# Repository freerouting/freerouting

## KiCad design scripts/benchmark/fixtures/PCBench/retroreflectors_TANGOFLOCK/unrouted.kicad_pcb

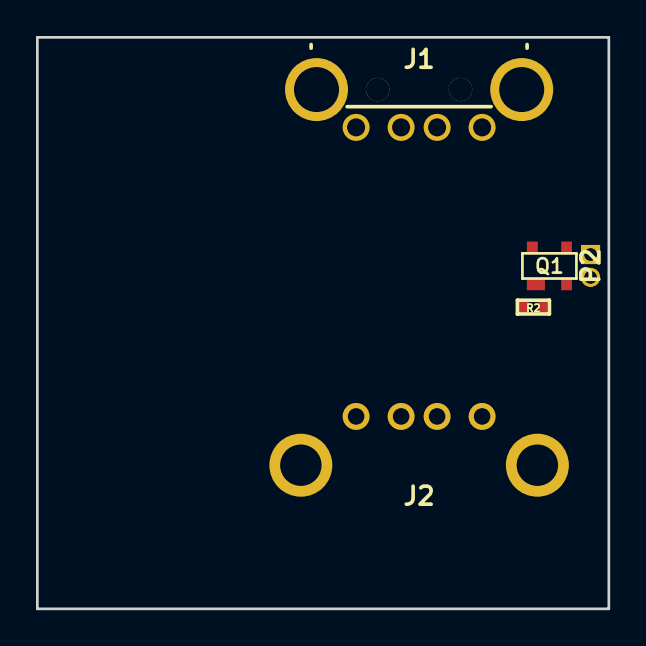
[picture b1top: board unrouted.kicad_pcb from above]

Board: 2 copper layers, 31.8 x 31.8 mm, 5 parts (0 on the bottom side), 6 nets, no tracks yet.

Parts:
J1: USB-DEVICE-SHIELD; GSG-USB-A-1001-010-01001-SHIELD
J2: USB-DEVICE-SHIELD; GSG-USB-A1HSW6
P2: ANTENNA; GSG-50MIL-HEADER-1x2-TH
Q1: MOSFET_N; GSG-SOT143B-GDS
R2: 10k; GSG-0402

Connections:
/DRAIN: P2.1, Q1.D
/GATE: J1.3, J2.3, Q1.G, R2.1
/SHIELD: J1.5, J2.5
GND: J1.4, J2.4, P2.2, Q1.B, Q1.S, R2.2
unnamed: J1.1, J2.1
unnamed: J1.2, J2.2

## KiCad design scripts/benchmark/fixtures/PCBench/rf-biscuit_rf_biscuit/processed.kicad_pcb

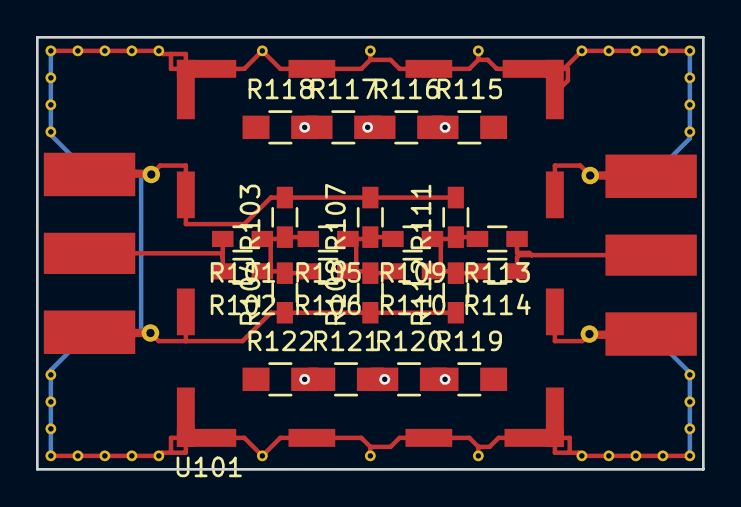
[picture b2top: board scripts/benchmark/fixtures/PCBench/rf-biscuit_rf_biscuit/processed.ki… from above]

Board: 2 copper layers, 37.0 x 24.0 mm, 25 parts (0 on the bottom side), 12 nets.

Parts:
P101, P102: BNC; SMA_EDGE_CONNECTOR
R101, R102, R103, R104, R105, R106, R107, R108, R109, R110, R111, R112, R113, R114: R; R_0603_HandSoldering
R115, R116, R117, R118, R119, R120, R121, R122: R; R_0805_HandSoldering
U101: 36103205_HF_Shield; 36103205-HF_Shield

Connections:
GND: P101.2, P102.2, R103.2, R104.1, R107.2, R108.1, R111.2, R112.1, U101.1
unnamed: P101.1, R101.2, R102.2
unnamed: P102.1, R113.1, R114.1
unnamed: R101.1, R102.1, R103.1, R104.2, R105.2, R106.2
unnamed: R105.1, R106.1, R107.1, R108.2, R109.2, R110.2
unnamed: R109.1, R110.1, R111.1, R112.2, R113.2, R114.2
unnamed: R115.1, R116.2
unnamed: R116.1, R117.2
unnamed: R117.1, R118.2
unnamed: R119.1, R120.2
unnamed: R120.1, R121.2
unnamed: R121.1, R122.2

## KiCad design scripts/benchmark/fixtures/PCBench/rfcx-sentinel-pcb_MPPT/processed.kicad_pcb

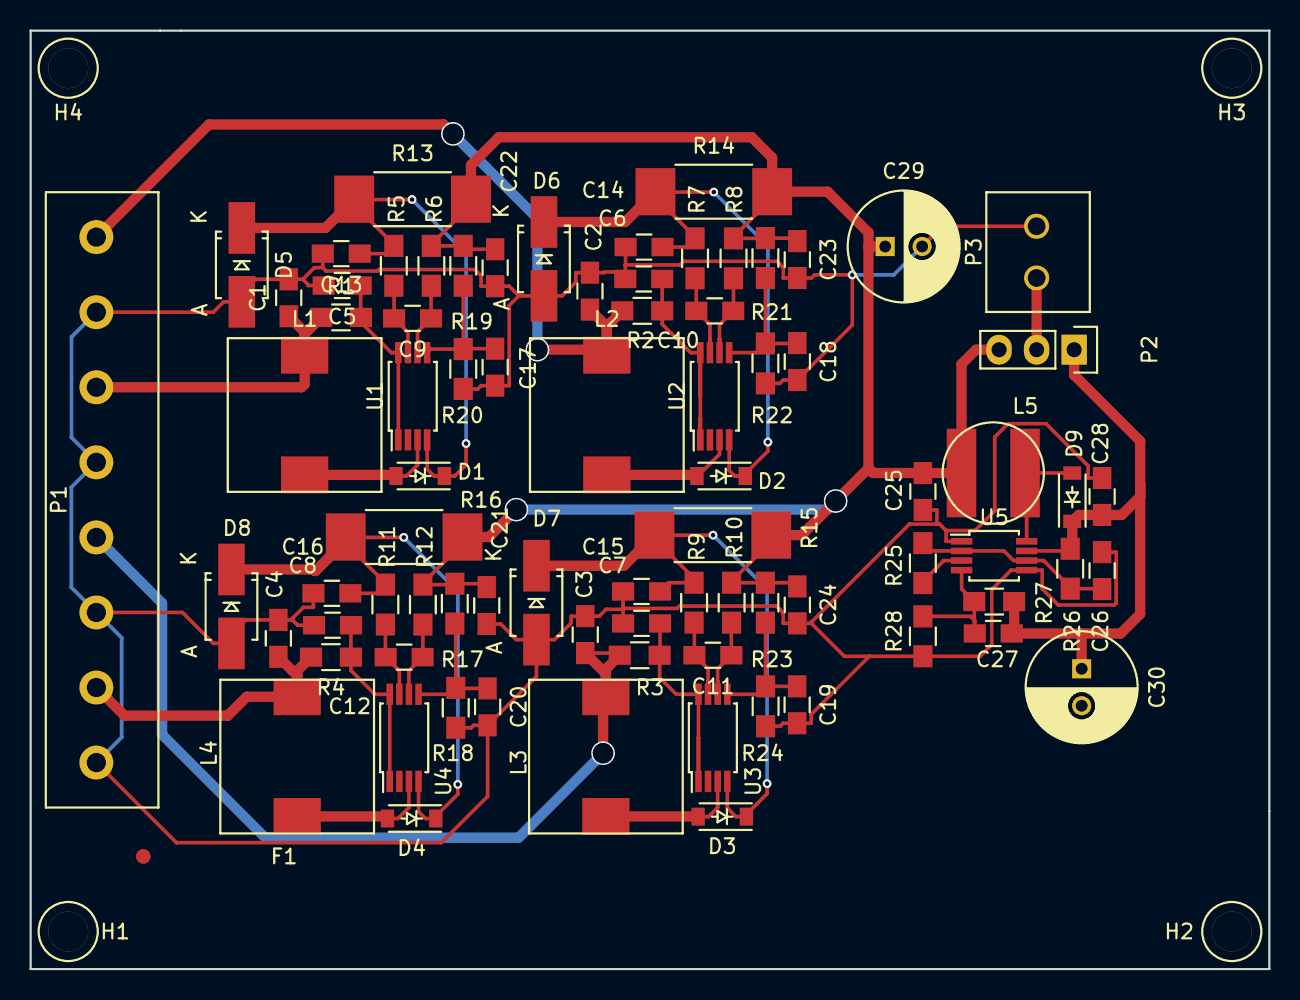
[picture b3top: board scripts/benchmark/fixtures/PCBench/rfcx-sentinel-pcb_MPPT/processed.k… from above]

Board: 2 copper layers, 83.8 x 63.5 mm, 86 parts (1 on the bottom side), 36 nets.

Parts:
C1, C2, C3, C4, C21, C22, C23, C24: 10uF; C_0805_HandSoldering
C5, C6, C7, C8: 100nF; C_0805_HandSoldering
C9, C10, C11, C12, C26: 1uF; C_0805_HandSoldering
C13, C14, C15, C16: 4.7uF; C_0805_HandSoldering
C17, C18, C19, C20: 1nF; C_0805_HandSoldering
C25: 22uF; C_0805_HandSoldering
C27: 39pF; C_0805_HandSoldering
C28: 68uF Tant; C_0805_HandSoldering
C29, C30: DNP; C_Radial_D7.5_L11.2_P2.5
D1, D2, D3, D4: 1n5819; SOD-123
D5, D6, D7, D8: Diode-TVS; Diode-SMA_Handsoldering
D9: 1N5819; SOD-123
F1: Fiducial; Fiducial_1mm_Dia_2.54mm_Outer_CopperTop
H1, H2, H3, H4: Mounting_Hole; Mnt_Hole
L1, L2, L3, L4: 10uH; Ind_10_4x10_4
L5: 6.8uF; Ind_6x6
Noname_1: Symbol_OSHW-Logo_SilkScreen
P1: CONN_01X08; Terminal_Block_8
P2: CONN_01X03; Pin_Header_Straight_1x03
P3: CONN_01X02; TerminalBlock_2
R1, R2, R3, R4, R5, R6, R7, R8, R9, R10, R11, R12: 1k; R_0805_HandSoldering
R13, R14, R15, R16: 0.5, 2W; R_2512_HandSoldering
R17, R19, R21, R23: 330K; R_0805_HandSoldering
R18, R20, R22, R24: 121K; R_0805_HandSoldering
R25: 200K; R_0805_HandSoldering
R26: 49.9; R_0805_HandSoldering
R27: 150K; R_0805_HandSoldering
R28: 49.9K; R_0805_HandSoldering
U1, U2, U3, U4: SPV1040; TSSOP-8_4.4x3mm_Pitch0.65mm
U5: LMR61428; MSOP-8_3x3mm_Pitch0.65mm

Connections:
/LM_FB: C27.1, R27.2, R28.1, U5.4
/MPPT_OUT: C21.1, C22.1, C23.1, C24.1, C25.1, C29.1, L5.1, P2.3, R6.2, R8.2, R10.2, R12.2, R13.2, R14.2, R15.2, R16.2, R17.1, R19.1, R21.1, R23.1
/Panel_Out_V: C27.2, C28.1, C30.1, D9.1, P2.1, R26.1, R27.1, U5.7
GND: C1.2, C2.2, C3.2, C4.2, C5.2, C6.2, C7.2, C8.2, C13.2, C14.2, C15.2, C16.2, C17.2, C18.2, C19.2, C20.2, C21.2, C22.2, C23.2, C24.2, C25.2, C26.2, C28.2, C29.2, D5.2, D6.2, D7.2, D8.2, P1.2, P1.4, P1.6, P1.8, P3.2, R18.2, R20.2, R22.2, R24.2, R28.2, U5.1, U5.5
unnamed: C1.1, L1.1, P1.3, R1.1
unnamed: C2.1, L2.1, P1.1, R2.1
unnamed: C3.1, L3.1, P1.5, R3.1
unnamed: C4.1, L4.1, P1.7, R4.1
unnamed: C5.1, R1.2, U1.1, U1.8
unnamed: C6.1, R2.2, U2.1, U2.8
unnamed: C7.1, R3.2, U3.1, U3.8
unnamed: C8.1, R4.2, U4.1, U4.8
unnamed: C9.1, R6.1, U1.6
unnamed: C9.2, R5.1, U1.7
unnamed: C10.1, R8.1, U2.6
unnamed: C10.2, R7.1, U2.7
unnamed: C11.1, R10.1, U3.6
unnamed: C11.2, R9.1, U3.7
unnamed: C12.1, R12.1, U4.6
unnamed: C12.2, R11.1, U4.7
unnamed: C13.1, D1.1, D5.1, R5.2, R13.1, U1.4
unnamed: C14.1, D2.1, D6.1, R7.2, R14.1, U2.4
unnamed: C15.1, D3.1, D7.1, R9.2, R15.1, U3.4
unnamed: C16.1, D4.1, D8.1, R11.2, R16.1, U4.4
unnamed: C17.1, R19.2, R20.1, U1.5
unnamed: C18.1, R21.2, R22.1, U2.5
unnamed: C19.1, R23.2, R24.1, U3.5
unnamed: C20.1, R17.2, R18.1, U4.5
unnamed: C26.1, R25.1, R26.2, U5.2, U5.6
unnamed: D1.2, L1.2, U1.3
unnamed: D2.2, L2.2, U2.3
unnamed: D3.2, L3.2, U3.3
unnamed: D4.2, L4.2, U4.3
unnamed: D9.2, L5.2, U5.8
unnamed: P2.2, P3.1
unnamed: R25.2, U5.3

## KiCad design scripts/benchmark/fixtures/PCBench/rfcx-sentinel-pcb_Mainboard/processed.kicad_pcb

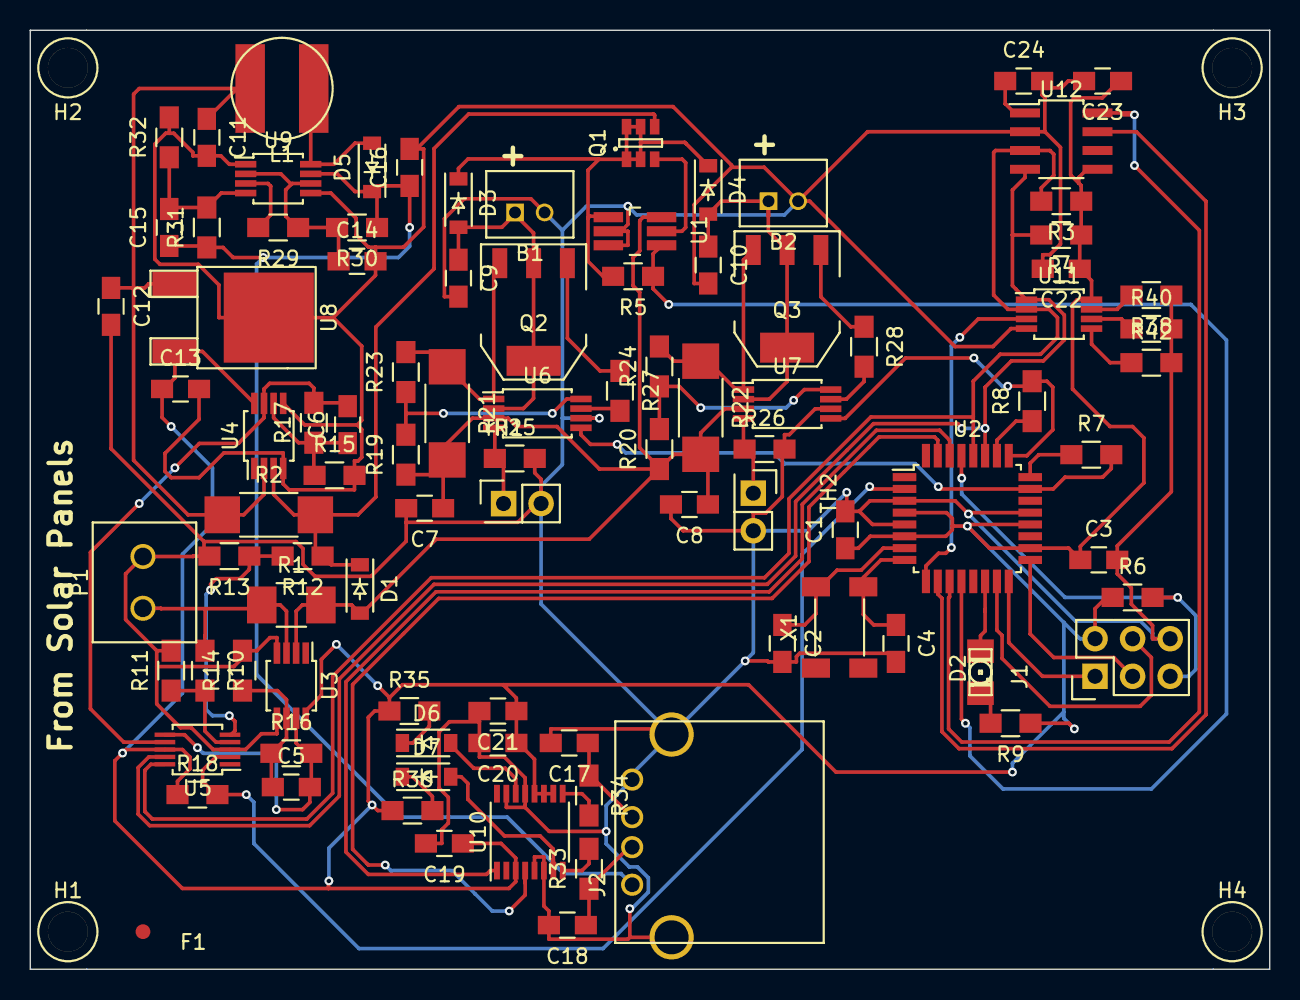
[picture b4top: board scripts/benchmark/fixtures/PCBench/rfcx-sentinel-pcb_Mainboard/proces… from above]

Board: 2 copper layers, 83.8 x 63.5 mm, 100 parts (1 on the bottom side), 64 nets.

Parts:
B1, B2: Li-ion(2Cell); JST_BAT
C1, C3, C12, C13, C14: 1uF; C_0805_HandSoldering
C2, C4: 6pF; C_0805_HandSoldering
C5, C6, C7, C8, C9, C10, C22: 0.1uF; C_0805_HandSoldering
C11: 22uF Tant; C_0805_HandSoldering
C15: 39pF; C_0805_HandSoldering
C16: 68uF Tant; C_0805_HandSoldering
C17, C18: 47pF; C_0805_HandSoldering
C19, C20: 100nF; C_0805_HandSoldering
C21: 4.7uF; C_0805_HandSoldering
C23: 0.22uF; C_0805_HandSoldering
C24: 0.1; C_0805_HandSoldering
D1, D3, D4: 1N5819; SOD-123
D2: LED; LED-1206
D5: Diode-Shottky; SOD-123
D6: GRN; SOD-123
D7: LED; SOD-123
F1: Fiducial; Fiducial_1mm_Dia_2.54mm_Outer_CopperTop
H1, H2, H3, H4: Mounting_Hole; Mnt_Hole
J1: ICSP; Pin_Header_Straight_2x03
J2: USB; USB_A
L1: 6.8uH; Ind_6x6
Noname_1: Symbol_OSHW-Logo_SilkScreen
P1: CONN_01X02; TerminalBlock_2
Q1: FDC638; FDC-SOT-23-6
Q2, Q3: FZT788B; SOT-223
R1: Res; R_1210_HandSoldering
R2: 0.5,1W; R_2010_HandSoldering
R3, R4, R6, R18, R19, R20, R38, R40, R42: 10k; R_0805_HandSoldering
R5: 470k; R_0805_HandSoldering
R7, R8, R27, R28: 1k; R_0805_HandSoldering
R9, R35, R36: 730; R_0805_HandSoldering
R10, R12: 1540; R_0805_HandSoldering
R11, R13: 2100; R_0805_HandSoldering
R14, R15, R29: 200k; R_0805_HandSoldering
R16: 2550; R_0805_HandSoldering
R17: Res; R_0805_HandSoldering
R21, R22: 0.2, 1W; R_2010_HandSoldering
R23, R24: 5k; R_0805_HandSoldering
R25, R26, R32: 49.9k; R_0805_HandSoldering
R30: 49.9; R_0805_HandSoldering
R31: 150k; R_0805_HandSoldering
R33, R34: 27; R_0805_HandSoldering
TH1, TH2: NTC; Pin_Header_Straight_2x01
U1: LTC4412; TSOT-6-MK06A_Handsoldering
U2: ATmega328P; TQFP-32_7x7mm_Pitch0.8mm
U3, U4: LTC6800; MSOP-8_3x3mm_Pitch0.65mm
U5: ADS1015; MSOP-10_3x3mm_Pitch0.5mm
U6, U7: bq2057CTS; TSSOP-8_4.4x3mm_Pitch0.65mm
U8: SM72238; DPAK-2
U9: LMR61428; MSOP-8_3x3mm_Pitch0.65mm
U10: FT230X; SSOP-16_3.9x4.9mm_Pitch0.635mm
U11: LM75BDP; MSOP-8_3x3mm_Pitch0.65mm
U12: HIH6130; HIH-SOIC-8
X1: 32kHz; SOJ-4

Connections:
+3V3: C1.1, C3.1, C13.1, C19.1, C20.1, C21.1, C22.1, C23.1, J1.2, R3.1, R4.1, R6.1, R9.1, R18.1, R35.1, R36.1, U2.4, U2.6, U2.18, U2.20, U3.8, U4.8, U5.8, U8.3, U10.3, U10.10, U10.11, U10.12, U11.8, U12.8
+5V: C15.1, C16.1, D5.1, J2.1, R30.1, R31.1, U9.7
/+3.3V and +5V Regulation/LM_FB: C15.2, R31.2, R32.1, U9.4
/ADC/Input-Current-H: P1.1, R1.1, R10.1, U3.3
/ADC/Input-Current-L: C7.1, C8.1, D1.2, R1.2, R19.1, R20.1, R21.2, R22.2, U1.6, U3.2, U6.3, U7.3
/ADC/Output-Current-H: D1.1, Q1.3, R2.2, R12.1, U4.3
/ADC/Output-Current-L: C11.1, C12.1, L1.1, R2.1, U4.2, U8.1
/Battery Management/Battery-Vout: D3.1, D4.1, Q1.1, R5.2, U1.1
/Environment Sensors/ENV_AL_H: U2.11, U12.5
/Environment Sensors/ENV_AL_L: U2.10, U12.6
/Environment Sensors/ENV_OS: U2.9, U11.3
/Microcontroller/AT-Alert: R18.2, U2.2, U5.2
/Microcontroller/AT-BAT1-STAT: R7.2, U2.23, U6.5
/Microcontroller/AT-BAT2-STAT: R8.2, U2.25, U7.5
/Microcontroller/AT-RXD: U2.30, U10.1
/Microcontroller/AT-SCL: R3.2, U2.28, U5.10, U11.2, U12.3
/Microcontroller/AT-SDA: R4.2, U2.27, U5.9, U11.1, U12.4
/Microcontroller/AT-TXD: U2.31, U10.4
/Microcontroller/PPM_STAT: R5.1, U1.4, U2.12
GND: B1.2, B2.2, C1.2, C2.2, C3.2, C4.2, C7.2, C8.2, C9.2, C10.2, C11.2, C12.2, C13.2, C14.2, C16.2, C17.2, C18.2, C19.2, C20.2, C21.2, C22.2, C23.2, C24.2, J1.6, J2.4, J2.5, P1.2, R11.2, R13.2, R14.2, R15.2, R25.2, R26.2, R32.2, R38.1, R40.2, R42.2, TH1.2, TH2.2, U1.2, U1.3, U2.3, U2.5, U2.21, U3.4, U3.5, U4.4, U4.5, U5.3, U6.6, U7.6, U8.2, U9.1, U9.5, U10.5, U10.6, U10.13, U10.15, U11.4, U12.2
unnamed: B1.1, C9.1, D3.2, Q2.2, Q2.4, U6.2
unnamed: B2.1, C10.1, D4.2, Q3.2, Q3.4, U7.2
unnamed: C2.1, U2.7, X1.1
unnamed: C4.1, U2.8, X1.4
unnamed: C5.1, R14.1, R16.1, U3.6
unnamed: C5.2, R16.2, U3.7, U5.6
unnamed: C6.1, R15.1, R17.1, U4.6
unnamed: C6.2, R17.2, U4.7, U5.7
unnamed: C14.1, R29.1, R30.2, U9.2, U9.6
unnamed: C17.1, J2.3, R34.1
unnamed: C18.1, J2.2, R33.1
unnamed: C24.1, U12.1
unnamed: D2.1, R9.2
unnamed: D2.2, U2.14
unnamed: D5.2, L1.2, U9.8
unnamed: D6.1, R35.2
unnamed: D6.2, U10.14
unnamed: D7.1, R36.2
unnamed: D7.2, U10.7
unnamed: J1.1, U2.16
unnamed: J1.3, U2.17
unnamed: J1.4, U2.15
unnamed: J1.5, R6.2, U2.29
unnamed: Q1.2, U1.5
unnamed: Q2.1, R27.1
unnamed: Q2.3, R21.1, R23.2, U6.1
unnamed: Q3.1, R28.1
unnamed: Q3.3, R22.1, R24.2, U7.1
unnamed: R7.1, U2.24
unnamed: R8.1, U2.26
unnamed: R10.2, R11.1, U5.4
unnamed: R12.2, R13.1, U5.5
unnamed: R19.2, R23.1, U6.8
unnamed: R20.2, R24.1, U7.8
unnamed: R25.1, TH1.1, U6.4
unnamed: R26.1, TH2.1, U7.4
unnamed: R27.2, U6.7
unnamed: R28.2, U7.7
unnamed: R29.2, U9.3
unnamed: R33.2, U10.8
unnamed: R34.2, U10.9
unnamed: R38.2, U11.7
unnamed: R40.1, U11.6
unnamed: R42.1, U11.5

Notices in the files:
scripts/benchmark/fixtures/PCBench/rf-biscuit_rf_biscuit/processed.kicad_pcb:
CC BY-SA 3.0
